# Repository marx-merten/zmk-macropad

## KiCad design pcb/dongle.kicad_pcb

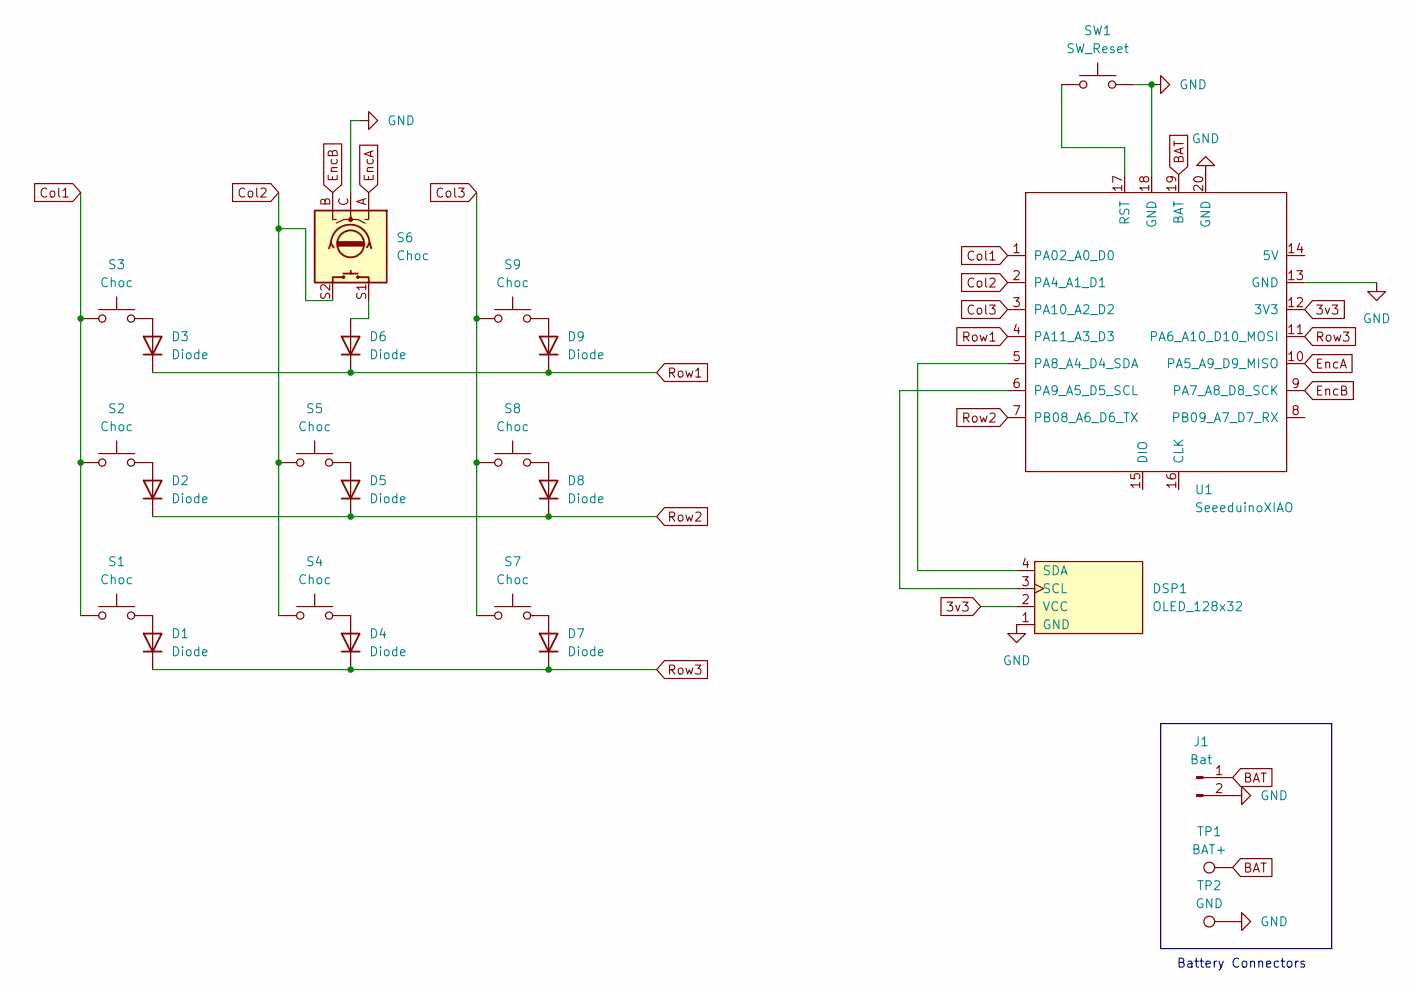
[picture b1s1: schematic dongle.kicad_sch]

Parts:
D1, D2, D3, D4, D5, D6, D7, D8, D9: Diode; D_SOD-123; MPN C493190; LCSC PartNumber C493190
DSP1: OLED_128x32
J1: Bat; JST_PH_S2B-PH-K_1x02_P2.00mm_Horizontal
S1, S2, S3, S4, S5, S7, S8, S9: Choc; Kailh_socket_PG1350; MPN C5333465; LCSC PartNumber C5333465
S6: Choc; RotaryEncoder_Alps_EC11E-Switch_Vertical_H20mm; Digi-Key_PN PEC11R-4215F-S0024-ND
SW1: SW_Reset; SW_SPST_EVQP7A; Part number Panasonic EVQ-P7A01P; LCSC PartNumber C2917474
TP1: BAT+; TestPoint_Pad_1.5x1.5mm
TP2: GND; TestPoint_Pad_1.5x1.5mm
U1: SeeeduinoXIAO; xiao-ble-smd-cutout

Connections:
3v3: DSP1.2 (VCC), U1.12 (3V3)
BAT: J1.1, TP1.1, U1.19 (BAT)
Col1: S1.1, S2.1, S3.1, U1.1 (PA02_A0_D0)
Col2: S4.1, S5.1, S6.S2, U1.2 (PA4_A1_D1)
Col3: S7.1, S8.1, S9.1, U1.3 (PA10_A2_D2)
EncA: S6.A, U1.10 (PA5_A9_D9_MISO)
EncB: S6.B, U1.9 (PA7_A8_D8_SCK)
GND: DSP1.1 (GND), J1.2, S6.C, SW1.2, TP2.1, U1.13 (GND), U1.18 (GND), U1.20 (GND)
unnamed: D1.2 (A), S1.2
unnamed: D2.2 (A), S2.2
unnamed: D3.2 (A), S3.2
unnamed: D4.2 (A), S4.2
unnamed: D5.2 (A), S5.2
unnamed: D6.2 (A), S6.S1
unnamed: D7.2 (A), S7.2
unnamed: D8.2 (A), S8.2
unnamed: D9.2 (A), S9.2
unnamed: DSP1.3 (SCL), U1.6 (PA9_A5_D5_SCL)
unnamed: DSP1.4 (SDA), U1.5 (PA8_A4_D4_SDA)
unnamed: SW1.1, U1.17 (RST)
Row1: D3.1 (K), D6.1 (K), D9.1 (K), U1.4 (PA11_A3_D3)
Row2: D2.1 (K), D5.1 (K), D8.1 (K), U1.7 (PB08_A6_D6_TX)
Row3: D1.1 (K), D4.1 (K), D7.1 (K), U1.11 (PA6_A10_D10_MOSI)

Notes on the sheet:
Battery Connectors

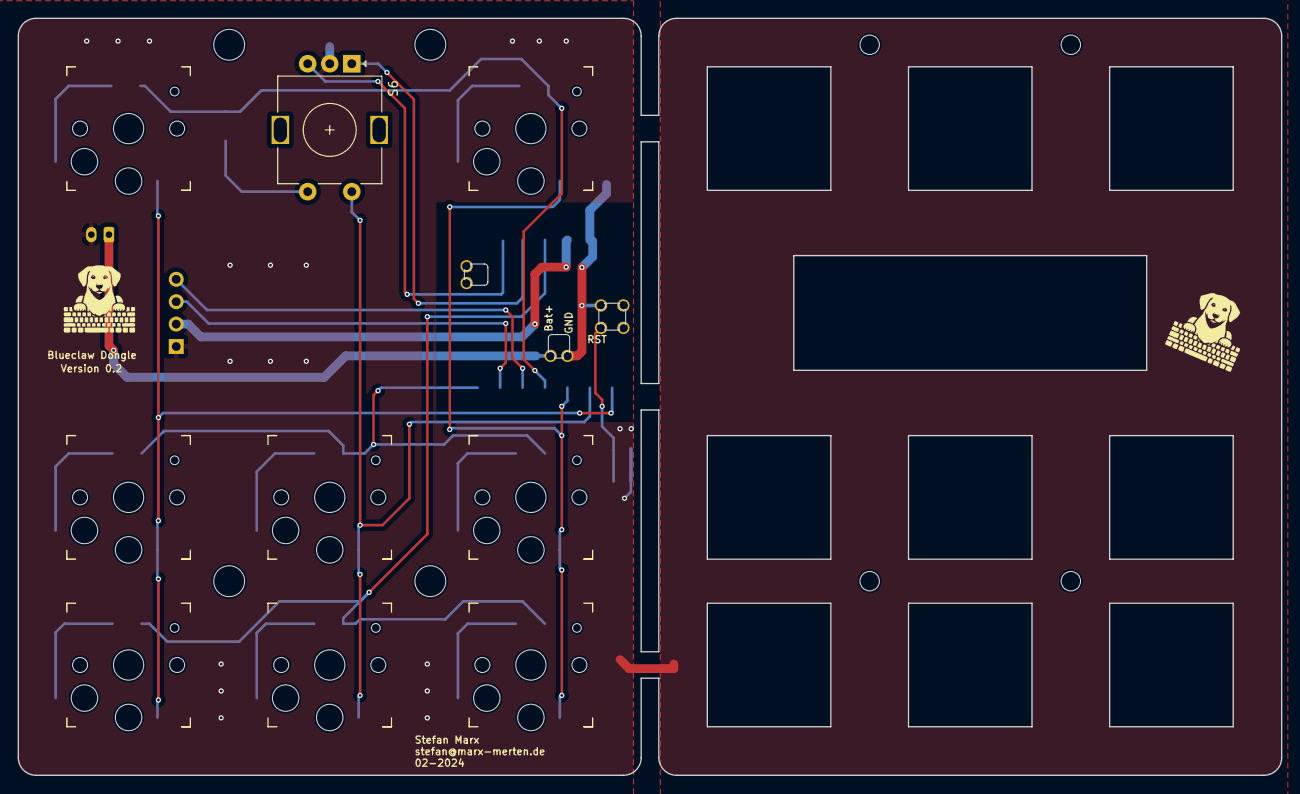
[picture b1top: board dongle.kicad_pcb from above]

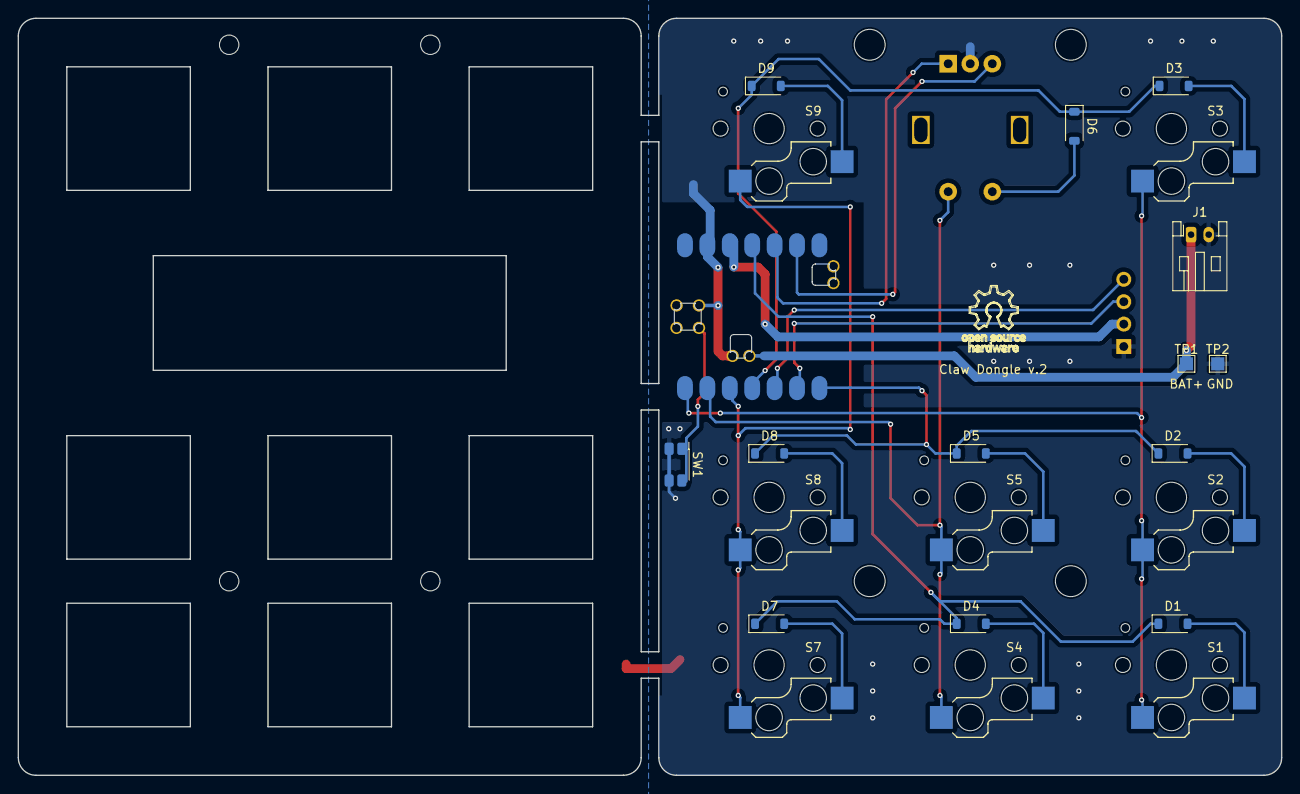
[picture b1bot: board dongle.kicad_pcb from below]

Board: 2 copper layers, 143.2 x 85.8 mm, 35 parts (15 on the bottom side), 23 nets.

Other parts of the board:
GL1, GL2: LOGO; DDKeyboard_10_10
Logo: Claw Dongle v.2; OSSLogo
M1, M2, M3, M4: MOUNT; MountingHole_3.5mm
M5, M6, M7, M8: MOUNT; MountingHole_2.2mm_M2_DIN965

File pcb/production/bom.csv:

Designator,Footprint,Quantity,Value,LCSC Part #
"D1, D2, D3, D4, D5, D6, D7, D8, D9",D_SOD-123,9,Diode,C493190
DSP1,OLED_128x32,1,OLED_128x32,
J1,JST_PH_S2B-PH-K_1x02_P2.00mm_Horizontal,1,Bat,
Logo,OSSLogo,1,Claw Dongle v.2,
"S1, S2, S3, S4, S5, S7, S8, S9",Kailh_socket_PG1350,8,Choc,C5333465
S6,RotaryEncoder_Alps_EC11E-Switch_Vertical_H20mm,1,Choc,
SW1,SW_SPST_EVQP7A,1,SW_Reset,C2917474
TP1,TestPoint_Pad_1.5x1.5mm,1,BAT+,
TP2,TestPoint_Pad_1.5x1.5mm,1,GND,
U1,xiao-ble-smd-cutout,1,SeeeduinoXIAO,

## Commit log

2024-03-03 INITIAL
2024-03-04 Init keyboard
2024-03-04 added ghAction build
2024-03-04 added configurator KKEEB Layout
2024-03-04 deleted format
2024-03-04 added transform
2024-03-04 added layout
2024-03-04 added bootloader
2024-03-04 renamed default layer
2024-03-04 tuned encoder settings
2024-03-30 added PCB
2024-03-30 added 3d designs
